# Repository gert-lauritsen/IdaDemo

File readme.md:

# Homeautomation fra pcb til produkt

## Beskrivelse

Vi vil forsøg på en aften at gå fra en ide til et produkt/prototype. Til formålet vil vi bruge Kicad, som vil blive gennemgået. Sende det til produktion monterer det og hælde kode i den. Til sidst vil vi lige se på WFF i homeautomation. Vi skal bl.a. se på dørlåse, automatiske gardiner og Automatisk lys.

* Kode på esp8266/esp32 i arduino IDE
* Udlægning af print med KIcad
* Mqtt og hvordan vi kan bruge det i automation
* Samarbejde via GitHUB

Niveauet bliver let så alle der har lyst til at prøve at udvikle deres egen print eller automatik, vil få en god start på deres produkt. Dette er for begynder, så bare kom og vær med.

Redskab bærbar med følgende installeret:
* [KiCad](https://kicad-pcb.org/download/)
* [Arduino](https://www.arduino.cc/)

Plan

* snakke om hvorfor og hvorfor ikke automation er smart
* Kicad gennemgang
* Kodning i arduino
* Samarbejde og deling via github

##Install ESP8266 på arduino
Under preference sætte følgede linie ind i additional boards:
https://dl.espressif.com/dl/package_esp32_index.json, http://arduino.esp8266.com/stable/package_esp8266com_index.json

Gå til Tools>Board>BoardManager søg efter esp8266 tryk install

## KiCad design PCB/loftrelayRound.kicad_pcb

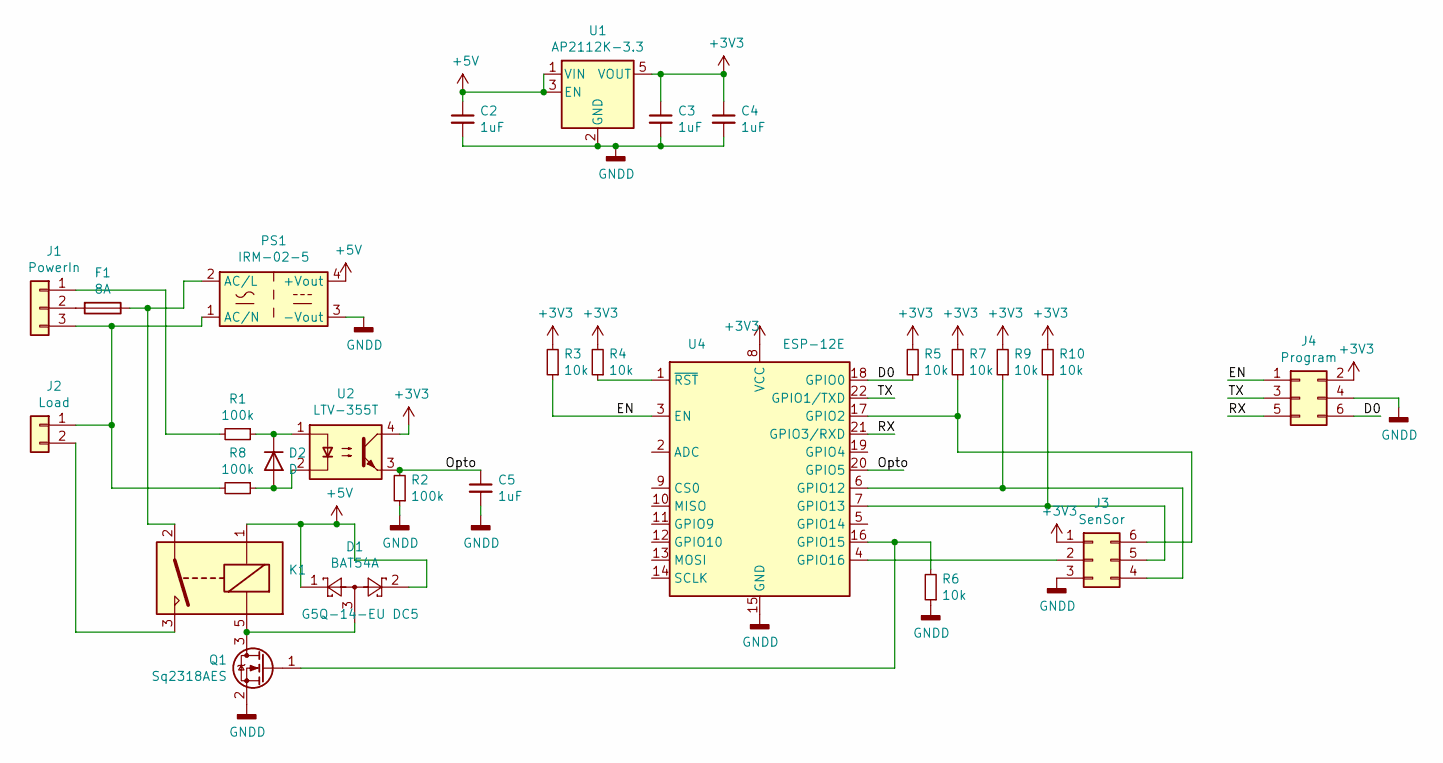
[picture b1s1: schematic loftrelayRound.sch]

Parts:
C2, C3, C4, C5: 1uF; C_0805_HandSoldering
D1: BAT54A; SOT-23
D2: D; D_1206
F1: 8A; Fuse_SMD
J1: PowerIn; Molex_Micro-Fit_3.0_43650-0315_1x03_P3.00mm_Vertical
J2: Load; Molex_Micro-Fit_3.0_43650-0215_1x02_P3.00mm_Vertical
J3: SenSor; Socket_Strip_Straight_2x03_Pitch2.54mm
J4: Program; Pin_Header_Straight_2x03_Pitch1.27mm_SMD
K1: G5Q-14-EU DC5; Relay_SPST_Omron-G5Q-1A
PS1: IRM-02-5; Converter_ACDC_MeanWell_IRM-02-xx_THT
Q1: Sq2318AES; SOT-23
R1, R8: 100k; R_1206_3216Metric
R2: 100k; R_0805_HandSoldering
R3, R4, R5, R6, R7, R9, R10: 10k; R_0805_HandSoldering
U1: AP2112K-3.3; SOT-23-5
U2: LTV-355T; SO-4_4.4x3.6mm_Pitch2.54mm
U4: ESP-12E

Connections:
+3V3: C3.1, C4.1, J3.1, J4.2, R3.2, R4.2, R5.2, R7.2, R9.2, R10.2, U1.5 (VOUT), U2.4, U4.8 (VCC)
+5V: C2.1, D1.1, D1.2, K1.1, PS1.4 (+Vout), U1.1 (VIN), U1.3 (EN)
/D0: J4.6, R5.1, U4.18 (GPIO0)
/EN: J4.1, R3.1, U4.3 (EN)
/Opto: C5.1, R2.2, U2.3, U4.20 (GPIO5)
/RX: J4.5, U4.21 (GPIO3/RXD)
/TX: J4.3, U4.22 (GPIO1/TXD)
GNDD: C2.2, C3.2, C4.2, C5.2, J3.3, J4.4, PS1.3 (-Vout), Q1.2 (S), R2.1, R6.1, U1.2 (GND), U4.15 (GND)
unnamed: D1.3, K1.5, Q1.3 (D)
unnamed: D2.1 (K), R1.1, U2.1
unnamed: D2.2 (A), R8.1, U2.2
unnamed: F1.1, K1.2, PS1.2 (AC/L)
unnamed: F1.2, J1.2
unnamed: J1.1, R1.2
unnamed: J1.3, J2.1, PS1.1 (AC/N), R8.2
unnamed: J2.2, K1.3
unnamed: J3.2, U4.4 (GPIO16)
unnamed: J3.4, R9.1, U4.6 (GPIO12)
unnamed: J3.5, R10.1, U4.7 (GPIO13)
unnamed: J3.6, R7.1, U4.17 (GPIO2)
unnamed: Q1.1 (G), R6.2, U4.16 (GPIO15)
unnamed: R4.1, U4.1 (~RST)

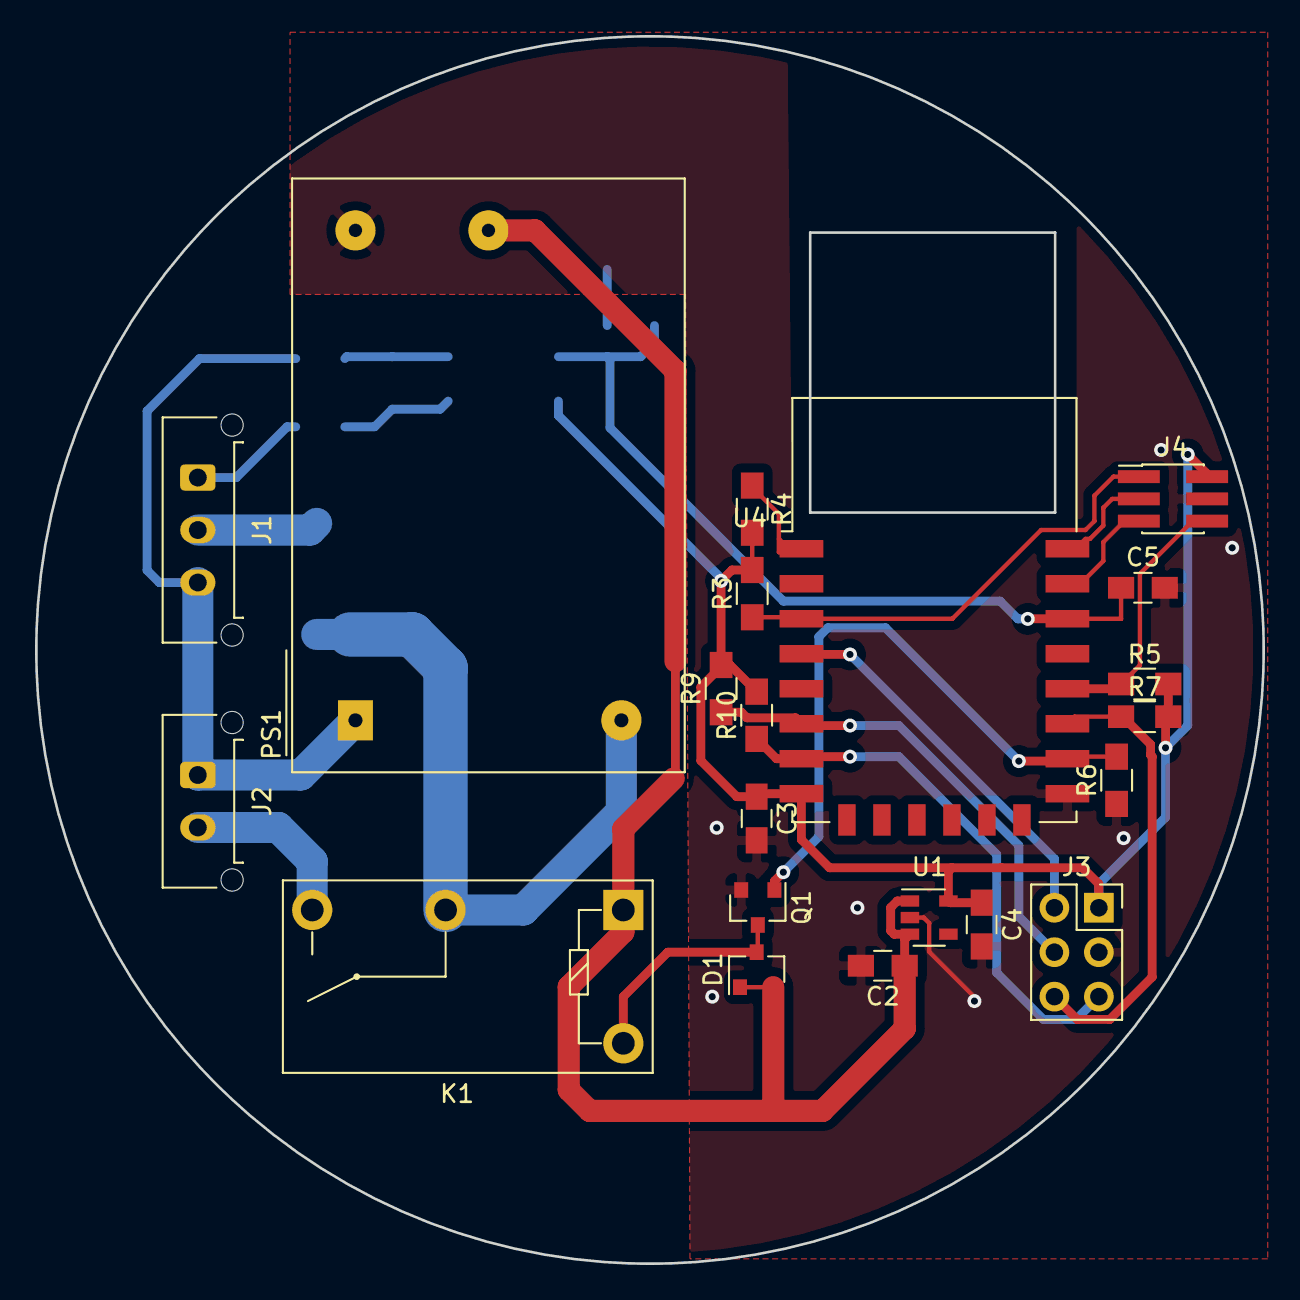
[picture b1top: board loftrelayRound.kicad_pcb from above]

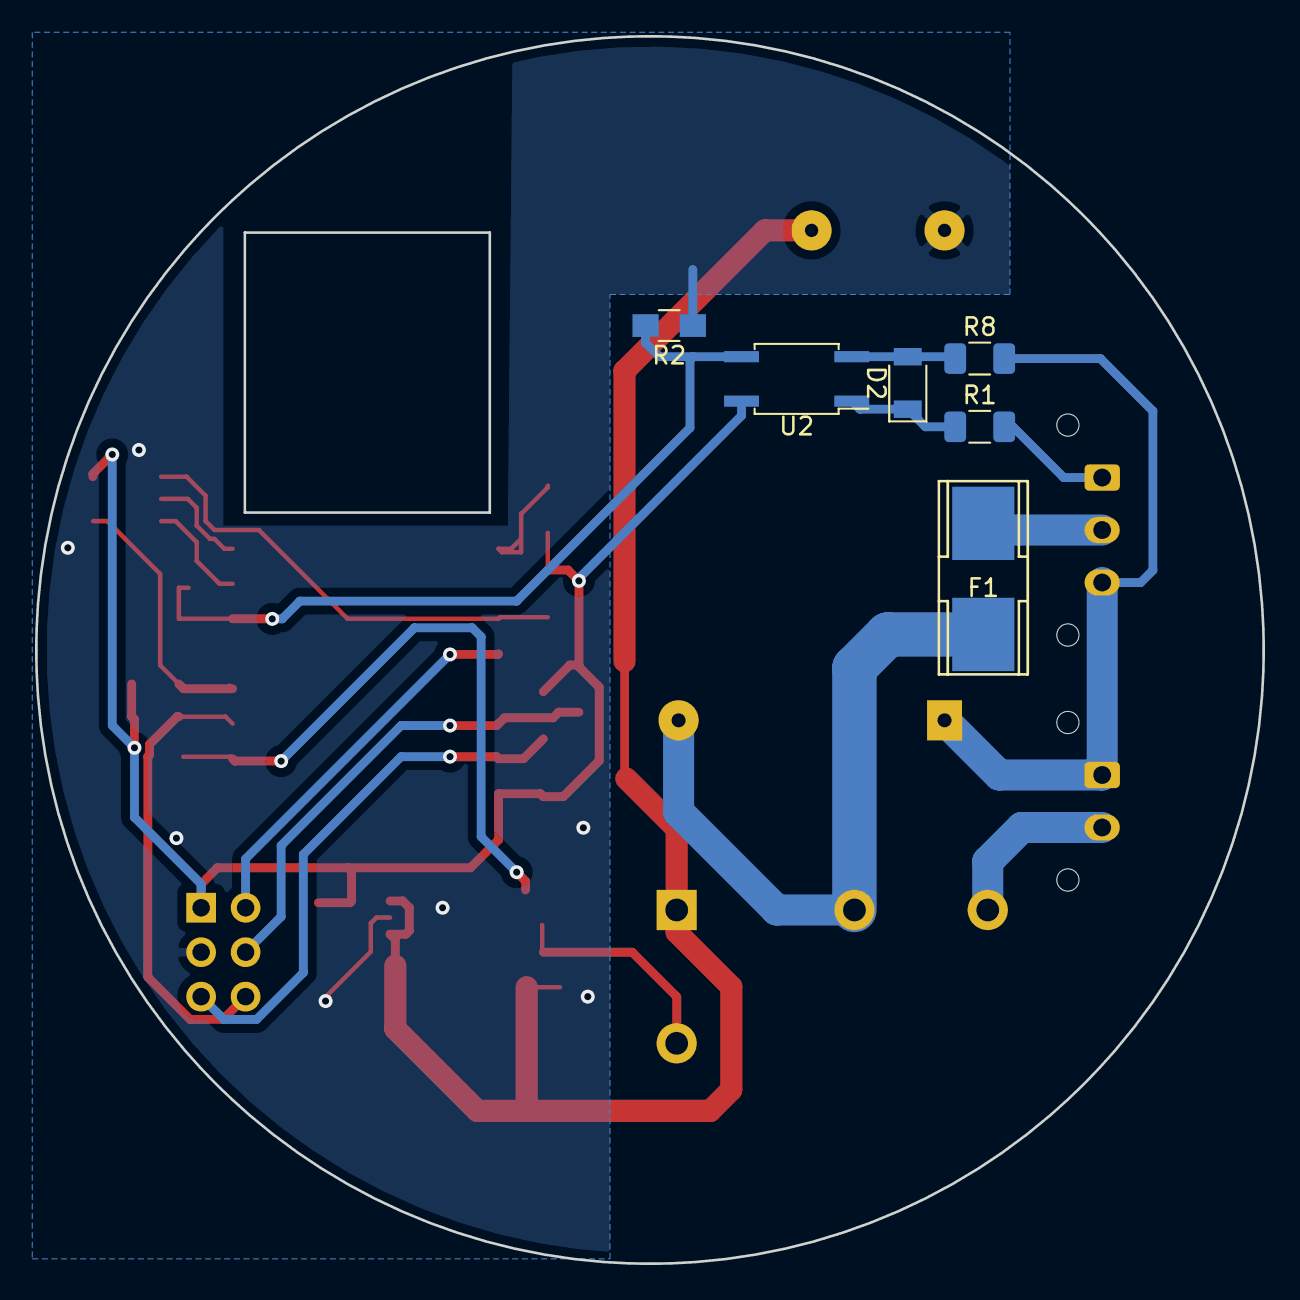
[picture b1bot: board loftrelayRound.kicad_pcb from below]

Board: 2 copper layers, 70.1 x 70.1 mm, 27 parts (6 on the bottom side), 22 nets.

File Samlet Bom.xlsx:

U2 | FT232RL-REEL | Package_SO:SSOP-28_5.3x10.2mm_P0.65mm | https://www.ftdichip.com/Support/Documents/DataSheets/ICs/DS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 | Active | Status | dk_Interface-Controllers | FT232RL-REEL | IC USB FS SERIAL UART 28-SSOP
J2 | Prog | Connector_PinHeader_1.27mm:PinHeader_2x03_P1.27mm_Vertical_SMD | ~ |  |  | Connector_Generic | Conn_02x03_Odd_Even | Generic connector, double row, 02x03, odd/even pin numbering scheme (row 1 odd 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
C4 | 100nF | Capacitor_SMD:C_0805_2012Metric | ~ |  |  | Device | C_Small | Unpolarized capacitor, small symbol
Q1 | BC846BS | Package_TO_SOT_SMD:SOT-363_SC-70-6 | https://assets.nexperia.com/documents/data-sheet/BC846BS.pdf |  |  | Transistor_BJT | BC846BS | 100mA IC, 65V Vce, Dual NPN/NPN Transistors, SOT-363
R5 | 10k | Resistor_SMD:R_0805_2012Metric | ~ |  |  | Device | R_Small | Resistor, small symbol
R6 | 10k | Resistor_SMD:R_0805_2012Metric | ~ |  |  | Device | R_Small | Resistor, small symbol
U1 | AP2112K-3.3 | Package_TO_SOT_SMD:SOT-23-5 | https://www.diodes.com/assets/Datasheets/AP2112.pdf |  |  | Regulator_Linear | AP2112K-3.3 | 600mA low dropout linear regulator, with enable pin, 3.8V-6V input voltage rang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
C2 | 1uF | Capacitor_SMD:C_0805_2012Metric | ~ |  |  | Device | C_Small | Unpolarized capacitor, small symbol
C3 | 1uF | Capacitor_SMD:C_0805_2012Metric | ~ |  |  | Device | C_Small | Unpolarized capacitor, small symbol
FB1 | Ferrite Bead | Inductor_SMD:L_0805_2012Metric | ~ |  |  | Device | Ferrite_Bead_Small | Ferrite bead, small symbol
C1 | 10nF | Capacitor_SMD:C_0805_2012Metric | ~ |  |  | Device | C_Small | Unpolarized capacitor, small symbol
D2 | LED | LED_SMD:LED_0805_2012Metric | ~ |  |  | Device | LED | Light emitting diode
D3 | LED | LED_SMD:LED_0805_2012Metric | ~ |  |  | Device | LED | Light emitting diode
R7 | 1k | Resistor_SMD:R_0805_2012Metric | ~ |  |  | Device | R_Small | Resistor, small symbol
R8 | 1k | Resistor_SMD:R_0805_2012Metric | ~ |  |  | Device | R_Small | Resistor, small symbol
SW1 | SW_Push | Button_Switch_SMD:SW_Push_1P1T_NO_6x6mm_H9.5mm | ~ |  |  | Switch | SW_Push | Push button switch, generic, two pins
SW2 | SW_Push | Button_Switch_SMD:SW_Push_1P1T_NO_6x6mm_H9.5mm | ~ |  |  | Switch | SW_Push | Push button switch, generic, two pins
J3 | USB_A | Connector_USB:USB_Mini-B_Wuerth_65100516121_Horizontal | ~ |  |  | Connector | USB_A | USB Type A connector
D1 | 82400102 | SOT95P280X145-6N | http://katalog.we-online.de/pbs/datasheet/82400102.pdf | 82400102 | Arrow Part Number | Programmer-rescue | 82400102-SamacSys_Parts
U2 | LTV-355T | Housings_SOIC:SO-4_4.4x3.6mm_Pitch2.54mm | https://www.mouser.dk/datasheet/2/239/LTV-355T%20Series-1308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 |  |  | Isolator | LTV-355T | Transistor Output Optocouplers Optocoupler Photodarlington
R1 | 33K | Resistor_SMD:R_1206_3216Metric | ~ |  |  | Device | R_Small | Resistor, small symbol
J1 | PowerIn | Connector_Molex:Molex_Micro-Fit_3.0_43650-0315_1x03_P3.00mm_Vertical | ~ |  |  | Connector_Generic | Conn_01x03 | Generic connector, single row, 01x03, script generated (kicad-library-utils/sch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
J2 | Load | Connector_Molex:Molex_Micro-Fit_3.0_43650-0215_1x02_P3.00mm_Vertical | ~ |  |  | Connector_Generic | Conn_01x02 | Generic connector, single row, 01x02, script generated (kicad-library-utils/sch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
U4 | ESP-12E | RF_Module:ESP-12E | http://wiki.ai-thinker.com/_media/esp8266/esp8266_series_mod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 |  |  | RF_Module | ESP-12E | 802.11 b/g/n Wi-Fi Module
R4 | 10k | Resistors_SMD:R_0805_HandSoldering | ~ |  |  | Device | R_Small | Resistor, small symbol
R3 | 10k | Resistors_SMD:R_0805_HandSoldering | ~ |  |  | Device | R_Small | Resistor, small symbol
R5 | 10k | Resistors_SMD:R_0805_HandSoldering | ~ |  |  | Device | R_Small | Resistor, small symbol
R6 | 10k | Resistors_SMD:R_0805_HandSoldering | ~ |  |  | Device | R_Small | Resistor, small symbol
R7 | 10k | Resistors_SMD:R_0805_HandSoldering | ~ |  |  | Device | R_Small | Resistor, small symbol
R2 | 100k | Resistors_SMD:R_0805_HandSoldering | ~ |  |  | Device | R_Small | Resistor, small symbol
Q1 | Sq2318AES | TO_SOT_Packages_SMD:SOT-23 | https://www.fairchildsemi.com/datasheets/2N/2N7002.pdf |  |  | Transistor_FET | 2N7002 | 0.115A Id, 60V Vds, N-Channel MOSFET, SOT-23
C2 | 1uF | Capacitors_SMD:C_0805_HandSoldering | ~ |  |  | Device | C_Small | Unpolarized capacitor, small symbol
C3 | 1uF | Capacitors_SMD:C_0805_HandSoldering | ~ |  |  | Device | C_Small | Unpolarized capacitor, small symbol
C4 | 1uF | Capacitors_SMD:C_0805_HandSoldering | ~ |  |  | Device | C_Small | Unpolarized capacitor, small symbol
D2 | D | Diodes_SMD:D_1206 | ~ |  |  | Device | D | Diode
K1 | G5Q-14-EU DC5 | Relay_THT:Relay_SPST_Omron-G5Q-1A | https://www.omron.com/ecb/products/pdf/en-g5q.pdf |  |  | Relay | G5Q-1A | Omron G5Q relay, Miniature Single Pole, SPST-NO, 10A
C5 | 1uF | Capacitors_SMD:C_0805_HandSoldering | ~ |  |  | Device | C_Small | Unpolarized capacitor, small symbol
PS1 | IRM-02-5 | Converter_ACDC:Converter_ACDC_MeanWell_IRM-02-xx_THT | http://www.meanwell.com/productPdf.aspx?i=675 |  |  | loftrelayRound-rescue | IRM-02-5-Converter_ACDC
J4 | Program | Pin_Headers:Pin_Header_Straight_2x03_Pitch1.27mm_SMD | ~ |  |  | Connector_Generic | Conn_02x03_Odd_Even | Generic connector, double row, 02x03, odd/even pin numbering scheme (row 1 odd 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
D1 | BAT54A | Package_TO_SOT_SMD:SOT-23 | http://www.diodes.com/_files/datasheets/ds11005.pdf |  |  | Diode | BAT54A | schottky barrier diode
F1 | 8A | SMD_Packages:Fuse_SMD | ~ |  |  | Device | Fuse | Fuse
J3 | SenSor | Socket_Strips:Socket_Strip_Straight_2x03_Pitch2.54mm | ~ |  |  | Connector_Generic | Conn_02x03_Counter_Clockwise | Generic connector, double row, 02x03, counter clockwise pin numbering scheme (s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
R9 | 10k | Resistors_SMD:R_0805_HandSoldering | ~ |  |  | Device | R_Small | Resistor, small symbol
R10 | 10k | Resistors_SMD:R_0805_HandSoldering | ~ |  |  | Device | R_Small | Resistor, small symbol
R8 | 100k/400V/0,25W | Resistor_SMD:R_1206_3216Metric | ~ |  |  | Device | R_Small | Resistor, small symbol
U1 | AP2112K-3.3 | Package_TO_SOT_SMD:SOT-23-5 | https://www.diodes.com/assets/Datasheets/AP2112.pdf |  |  | Regulator_Linear | AP2112K-3.3 | 600mA low dropout linear regulator, with enable pin, 3.8V-6V input voltage rang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

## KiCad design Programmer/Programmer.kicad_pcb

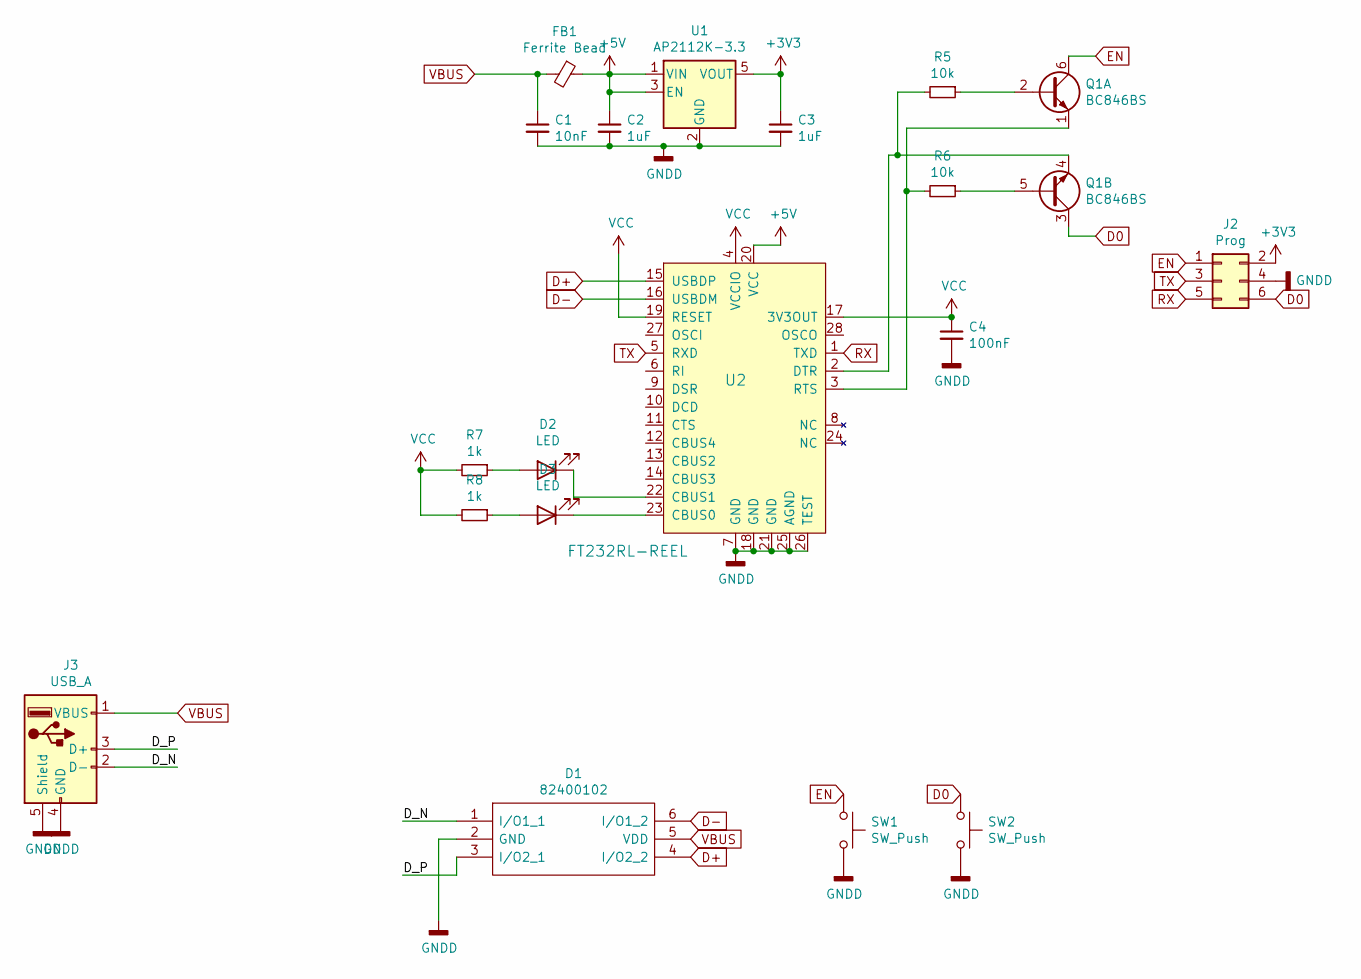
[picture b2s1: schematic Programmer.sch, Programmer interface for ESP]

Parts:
C1: 10nF; C_0805_2012Metric
C2, C3: 1uF; C_0805_2012Metric
C4: 100nF; C_0805_2012Metric
D1: 82400102; SOT95P280X145-6N; Manufacturer_Part_Number 82400102; Mouser Part Number 710-82400102
D2, D3: LED; LED_0805_2012Metric
FB1: Ferrite Bead; L_0805_2012Metric
J2: Prog; PinHeader_2x03_P1.27mm_Vertical_SMD
J3: USB_A; USB_Mini-B_Wuerth_65100516121_Horizontal
Q1: BC846BS; SOT-363_SC-70-6
R5, R6: 10k; R_0805_2012Metric
R7, R8: 1k; R_0805_2012Metric
SW1, SW2: SW_Push; SW_Push_1P1T_NO_6x6mm_H9.5mm
U1: AP2112K-3.3; SOT-23-5
U2: FT232RL-REEL; SSOP-28_5.3x10.2mm_P0.65mm; MPN FT232RL-REEL; Digi-Key_PN 768-1007-1-ND

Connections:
+3V3: C3.1, J2.2, U1.5 (VOUT)
+5V: C2.1, FB1.1, U1.1 (VIN), U1.3 (EN), U2.20 (VCC)
/D_N: D1.1 (I/O1_1), J3.2 (D-)
/D_P: D1.3 (I/O2_1), J3.3 (D+)
D0: J2.6, Q1.3 (C2), SW2.1
D+: D1.4 (I/O2_2), U2.15 (USBDP)
D-: D1.6 (I/O1_2), U2.16 (USBDM)
EN: J2.1, Q1.6 (C1), SW1.1
GNDD: C1.2, C2.2, C3.2, C4.2, D1.2 (GND), J2.4, J3.4 (GND), J3.5 (Shield), SW1.2, SW2.2, U1.2 (GND), U2.7 (GND), U2.18 (GND), U2.21 (GND), U2.25 (AGND), U2.26 (TEST)
unnamed: D2.1 (K), U2.22 (CBUS1)
unnamed: D2.2 (A), R7.1
unnamed: D3.1 (K), U2.23 (CBUS0)
unnamed: D3.2 (A), R8.1
unnamed: Q1.1 (E1), R6.2, U2.3 (RTS)
unnamed: Q1.2 (B1), R5.1
unnamed: Q1.4 (E2), R5.2, U2.2 (DTR)
unnamed: Q1.5 (B2), R6.1
RX: J2.5, U2.1 (TXD)
TX: J2.3, U2.5 (RXD)
VBUS: C1.1, D1.5 (VDD), FB1.2, J3.1 (VBUS)
VCC: C4.1, R7.2, R8.2, U2.4 (VCCIO), U2.17 (3V3OUT), U2.19 (RESET)

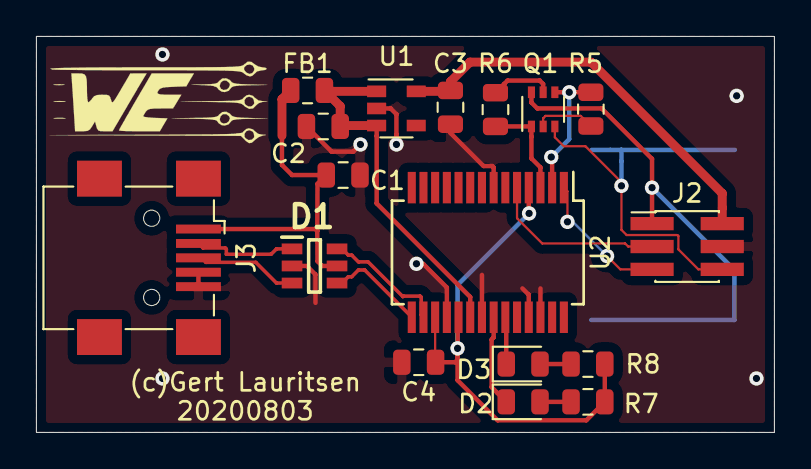
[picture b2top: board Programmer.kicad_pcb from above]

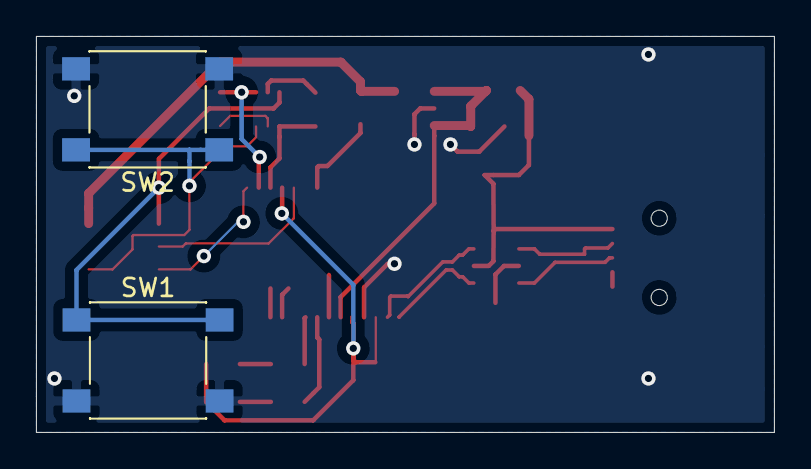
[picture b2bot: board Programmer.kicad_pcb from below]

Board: 2 copper layers, 41.0 x 22.0 mm, 19 parts (2 on the bottom side), 21 nets.

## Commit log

2020-06-11 Init
2020-07-29 Ændret stik
    Har ændret til til 3mm mikrofit fjernet C ved optocobler for at undgå stød.
2020-07-29 Ændret password
2020-08-03 Update af komponeter samt ny programmer
2020-08-03 Rettelse på programmer vcc
2020-08-03 Ændret track,
    således at vi ved 5A får en max temperatur forøgelse på 10°C
2020-08-03 link til eso8266 i arduino
2020-08-04 knap tilføjet
2020-08-05 3d footprint
2020-09-03 Final edit
    Ændret LDO , da jeg ikke kunne skaffe den anden på mouser kun i kina, hvilket jeg ikke har tid til. Rettet en bane der kom lidt for tæt og fejlede i første forsøg
2020-09-16 opstart
    Sender en status ved opstart
2020-09-18 Update referance
2020-09-18 Tilføjet powerpoint
